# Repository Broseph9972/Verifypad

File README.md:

# VerifyPad

(PDF FORMAT FOR HACK CLUB)[579592197-c25e6422-f377-4141-9c7b-d6e0fb70b0fa.pdf](https://github.com/user-attachments/files/27544661/579592197-c25e6422-f377-4141-9c7b-d6e0fb70b0fa.pdf)

# About
Simple macropad for [Hack club fallout](https://fallout.hackclub.com/)

It uses a simple desktop app to check your email every 3 seconds and check for OTP codes/links. You press the left button to paste an OTP and the right button to paste a verification link. It uses a program you install on your computer to check your email and paste codes.

We decided to make it to save effort when pasting email codes because it can be very annoying and it's much easier to just press a button and have it done for you. 

we made it by just doing an hour of work each day until everything worked. joe did pcb and brad did code and case. joe still cant code :( he gonna learn tho :)

# Motivation
We were motivated to make this project because all the time it takes to open your email for a OTP adds up, and it would be really nice to click a button to get an OTP code. Also we got it done really quickly because we both set a 14 day streak goal and didn't want to lose it. We're really exited to put it together!

# Bill of Materials (BOM)

|Id |Name                  |Footprint|Quantity|Description|Supplier and Ref                                   |Price  |
|---|----------------------|---------|--------|-----------|---------------------------------------------------|-------|
|1  |Switches              |         |2       |           |https://www.amazon.com/s?k=cherry+mx+switches      |<$0.50 |
|1  |Keycaps               |         |2       |           |https://www.amazon.com/s?k=mx+keycaps              |<$0.50 |
|2  |XIAO-RP2040-DIP       |         |1       |           |https://www.seeedstudio.com/XIAO-RP2040-p-5026.html|$4.99  |
|3  |Waveshare 0.49 Display|         |1       |           |https://www.waveshare.com/0.49inch-lcd-module.htm  |$5.99  |
|4  |PCB                   |         |1       |           |https://jlcpcb.com/                                |$3.12  |
|5  |3D printed parts      |         |?       |           |                                                   |$0.00  |
|   |Total Cost            |         |        |           |                                                   |~$16.10|

# Design
### PCB

### Assembly Video

below is an assembly video for the 3d printed files. you should solder the xiao and switches into their outlined spots, solder the screen on with wires and slot it into the lid, then flash the firmware.

[https://raw.githubusercontent.com/Broseph9972/Verifypad/main/media/assembly.mp4
](https://github.com/user-attachments/assets/6515c9df-35d1-4015-a47c-1bd419035557)

# Downloading Software
If you're on windows, use the installer in releases and it will automatically install the program, as well as adding it to path and creating a system task to run it on login.
If you're on another OS or the installer doesn't work (very likely) you can also clone the repo, go to the application folder, and run verifypad.py.

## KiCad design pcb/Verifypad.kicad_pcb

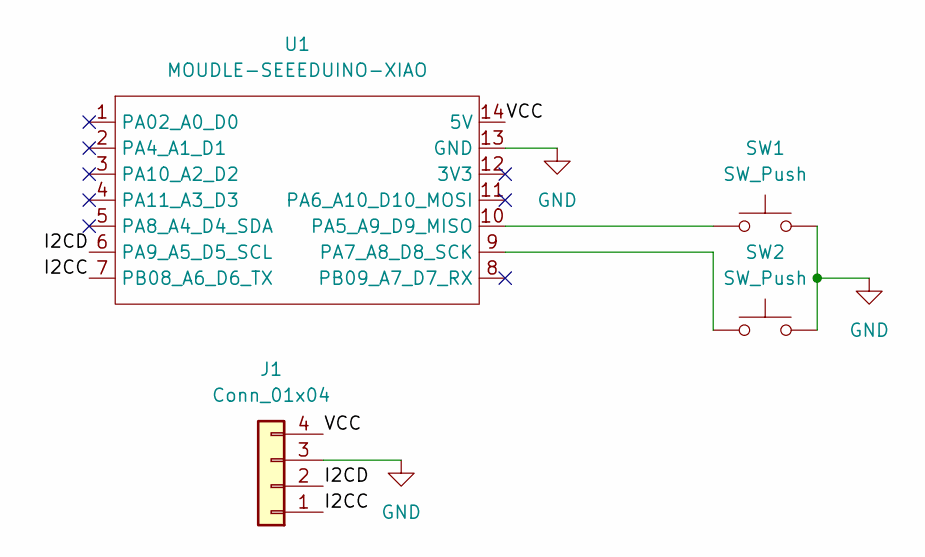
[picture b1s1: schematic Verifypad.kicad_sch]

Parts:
J1: Conn_01x04; PinHeader_1x04_P2.54mm_Vertical
SW1, SW2: SW_Push; SW_Cherry_MX_1.00u_PCB
U1: MOUDLE-SEEEDUINO-XIAO; XIAO-RP2040-DIP

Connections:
/I2CC: J1.1, U1.7 (PB08_A6_D6_TX)
/I2CD: J1.2, U1.6 (PA9_A5_D5_SCL)
/VCC: J1.4, U1.14 (5V)
GND: J1.3, SW1.2, SW2.2, U1.13 (GND)
unnamed: SW1.1, U1.10 (PA5_A9_D9_MISO)
unnamed: SW2.1, U1.9 (PA7_A8_D8_SCK)

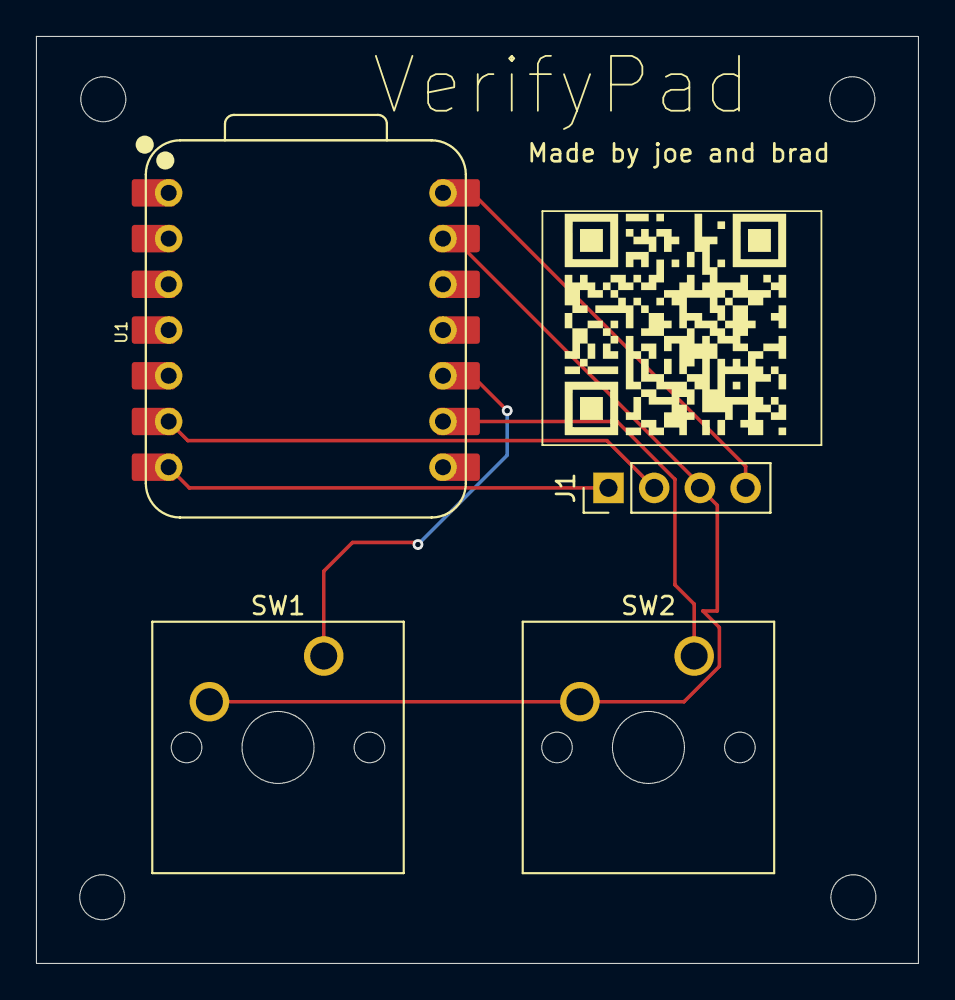
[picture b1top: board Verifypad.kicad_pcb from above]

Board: 2 copper layers, 49.0 x 51.5 mm, 5 parts (0 on the bottom side), 6 nets.

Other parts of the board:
Waveshare 0.49" Display: 0.49Display

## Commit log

2026-04-12 added the thingy to read emails
2026-04-12 added kicad files
2026-04-12 added gitignore and fixed auth.json location
2026-04-12 fixed gitignore
2026-04-12 added functions to get the latest otp or link
2026-04-12 PCB render
2026-04-13 Kicad
    new kicad stuff :)
2026-04-13 added pasting
2026-04-13 improved tests
2026-04-13 bug fix
2026-04-13 added requirements.txt
2026-04-13 changed auth.json to a general config.json
2026-04-13 added config test
2026-04-13 added stuff to config.py
2026-04-13 improved config test and added list of tests at the top
2026-04-13 added a module to manage the serial communication
2026-04-13 finished all the code except for the 500 bugs that probobly exist
2026-04-13 changed sizing and got STL
2026-04-13 PCbbbbadsadldj
2026-04-13 code :)
2026-04-13 added the realy really bad logo
2026-04-13 added some stuff
2026-04-14 Rename
2026-04-14 fixed main.py
2026-04-14 stuff
2026-04-14 added installer
2026-04-14 fix bradley error
2026-04-14 deleted stuff we dont need
2026-04-14 shitty ai website
2026-04-14 fixed installer
2026-04-14 changed gitignore
2026-04-14 Readme kinda
    Updated README to include images and project description.
2026-04-14 Revise PCB description in README
    Updated README to improve clarity and formatting.
2026-04-14 tried to add stuff to installer. adding to path still doesnt work and it gets an error when installed into program files and trying to read the config file
2026-04-15 made it store the config file in appdata
2026-04-15 Enhance README with component table and description
    Added a table with component details and updated project description.
2026-04-15 Added bom
2026-04-17 added zine
2026-04-17 Update README with BOM and cost estimation
    Added a Bill of Materials (BOM) section with estimated total cost.
2026-04-17 added qr code to the pcb silkscreen
2026-04-17 site
2026-04-18 made simple gui with quit button for testing
2026-04-18 added icon to it
2026-04-18 migrated from cli to gui
2026-04-18 fixed email getter it works now
2026-04-18 get rid of stinky gui
2026-04-18 added running in background
2026-04-18 updated gitignore
2026-04-18 install script working
2026-04-18 added cool art and fixed running in background thingy
2026-04-18 fixed bug and now i gotta compile again nooo
2026-04-18 re-compiled installer
2026-04-18 Update email check interval to every 3 seconds
2026-04-18 Update README to remove future reprogramming plans
    Removed future plans for reprogramming the device.
2026-04-18 Clarify future reprogramming plans in README
    Updated README to clarify future plans regarding reprogramming.
2026-04-18 I fixed the installinator and now it actually works yay
2026-04-18 added bitmaps for the screen
2026-04-18 added firmware
2026-04-18 added arduino code
2026-04-18 fixed code
2026-04-18 added some code
2026-04-18 refactor display logic and add main application structure
2026-04-18 added libraries
2026-04-18 fix bug
2026-04-18 added codes
2026-04-18 bugfix #2
2026-04-18 ai slop that makes text go on screen wahoo
2026-04-19 removed mean message
2026-04-19 added backslash n to mesages sent with serial
2026-04-19 recompiled installer
2026-04-19 got rid of joes ai slop
2026-04-19 moved bitmaps
2026-04-19 fixed some codes
2026-04-19 Made HID firmware which would never be used for geometrical dash
2026-04-19 got the microcontroller code owrking
2026-04-19 rename folder
2026-04-19 added .history to gitignore
2026-04-19 Revise BOM and clean up README content
    Updated BOM to reflect correct designator names and removed unnecessary text.
2026-04-20 added media folder
2026-04-20 added stl's
2026-04-20 added f3d file
2026-04-20 Rename Screenshot 2026-04-20 183132.png to verifypad.png
2026-04-20 Add assembly video link to README
    Added a link to an assembly video in the README.
2026-04-20 Fix media link in README
    Updated media link to point to a new asset location.
2026-04-20 final final final pcb
2026-04-20 Revise README with project info and BOM updates
    Updated project details, added images, and refined BOM.
2026-04-20 Update README with project motivation and development notes
    Added a personal touch to the project description and clarified the development process.
2026-04-20 Add 3D printed parts to the cost table
2026-04-20 Clean up BOM table and correct total price
    Agent-Logs-Url: https://github.com/Broseph9972/Verifypad/sessions/b39da4b6-02ad-424b-b639-aa867b7c5642
2026-04-20 Clarify BOM total as a price range
    Agent-Logs-Url: https://github.com/Broseph9972/Verifypad/sessions/b39da4b6-02ad-424b-b639-aa867b7c5642
2026-04-20 Add bom.csv from README BOM table
    Agent-Logs-Url: https://github.com/Broseph9972/Verifypad/sessions/5820b9da-cfd1-42d8-a7e5-a62fd134f400
2026-04-20 Revise README for improved clarity and tone
    Reworded the explanation of the project's purpose and development process for clarity.
2026-04-20 Add supplier links to BOM CSV entries
    Agent-Logs-Url: https://github.com/Broseph9972/Verifypad/sessions/47d12a3b-9dad-4c9f-8764-07e86cdb376b
2026-04-20 Include assembly video link in README
    Added assembly video instructions for 3D printed files.
2026-04-21 Update README with software downloading instructions
    Added instructions for downloading software on different operating systems.
2026-04-21 removed main.py bc it has the stinky gui
2026-04-21 updated installer
2026-04-28 Update project contribution details in README
2026-04-28 Fix pronouns and enhance README clarity
    Corrected pronouns and improved clarity in the project description.
2026-04-28 Add motivation section to README
    Added motivation section to explain project purpose.
2026-04-28 Update motivation section in README
    Revised motivation section for clarity and added excitement about project completion.
2026-04-28 Update BOM with new component names and prices
2026-04-28 Revise BOM prices and total cost
    Updated prices for Cherry MX Clear and SparkFun keycap in BOM. Adjusted total cost accordingly.
2026-04-28 Update PCB link in the README
2026-05-09 Updated CSV
